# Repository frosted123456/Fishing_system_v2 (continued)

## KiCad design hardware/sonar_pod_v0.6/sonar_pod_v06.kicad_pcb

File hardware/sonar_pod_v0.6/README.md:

# Sonar pod board v0.6: all JLC parts on top, ESP32 module on the bottom

Status: generated, not ordered, not reviewed by a human. DRC: 0 unconnected, 0 clearance (silkscreen and library warnings only).
Netlist check: every pad matches design.py (0 mismatches).
Board: 58 x 53 mm (same as v0.5), 4 layers (F signal / In1 GND / In2 GND / B signal), 1.6 mm, HASL lead-free.

## What changed vs v0.5

| Area | v0.5 | v0.6 | Why |
|---|---|---|---|
| LoRa Ra-01SH (+ C36, C37, R29) | bottom, hand-soldered | **top, JLC-assembled** (lora variant) | one machine-assembled side for everything JLC can place |
| ESP32-S3 module | top, hand-soldered | **bottom, hand-soldered**, under the LoRa module | the only SMD part you solder yourself |
| External ADC (ADS7042 + 5 parts) | DNP option | **removed** | not worth it: the 80 µs ping limits resolution more than the 83 kHz internal ADC; it also lengthened VOUT_I |
| VOUT_I (TUSS → filter) | 26.8 mm, 2 vias | **9.9 mm, 0 vias** | ADC branch and TP3 stub gone |
| TP3 (VOUT test pad) | yes | removed | probe the envelope on R11 |
| Connector pin names | none | **on the silkscreen**: J1 BAT+/BAT−, J2 XA/XB/SH/NTC/NG, J3 3V3/GND/HALL, J4 3V3/GND/BTN/LED, P1 DA/DB/VTX/GND/XA/XB | what to solder where |
| Bottom paste layer | in the gerbers | **removed** | nothing on the bottom is machine-soldered, so no bottom stencil is needed |
| TUSS SPI / IO pin map | see v0.5 | **changed** (see below) | the bottom-mounted module is mirrored, so the bus order flips |

## Orders

| Variant | Assembled parts | BOM lines | Extended types (fee each) |
|---|---|---|---|
| tipup | 59 | 32 | 6: TUSS4470, TPS63020, MT3608, L1, L2, USB-C |
| lora | 63 | 33 | 7: the same + Ra-01SH |

## Noise audit (`src/noise_audit.py`)

| Check | v0.5 | v0.6 |
|---|---|---|
| INP / INN / RINP / FLT | 3.2 / 4.1 / 6.3 / 3.9 mm, 0 vias | 3.2 / 4.1 / 6.0 / 3.9 mm, 0 vias |
| VOUT_I | 26.8 mm, 2 vias, 11 % without reference | **9.9 mm, 0 vias, 0 %** |
| VOUT (to the ESP32 ADC) | 9.5 mm, 0 vias | 10.2 mm, 1 via (the ESP32 pad is on the bottom) |
| GND vias / ground >8 mm from a stitch | 141 / 2 % | 154 / 0 % |
| MT3608 loop / switch node | 4.9 mm² / 6.9 mm | 4.9 mm² / 5.7 mm |
| SGND | 40 mm, 2 vias | 32 mm, 3 vias |
| USB D+ / D− length | 12 / 15 mm | **32 / 36 mm** |

Parallel runs worth knowing about:

| Victim | Aggressor | Run / gap | Assessment |
|---|---|---|---|
| RINP | OUTA | 4.3 mm at 0.54 mm | Harmless. In direct drive OUTA *is* the transducer line that feeds RINP, and OUTA is idle during receive. Transformer mode: gate pulses happen only during transmit. |
| NTC_ADC | SCLK / USB / SDI / SDO | ≤3.8 mm each | slow DC signal with a 100 nF filter |

USB is longer because the module's USB pins now sit at its bottom-right corner. That's fine for full-speed USB at 12 Mbit/s, which tolerates far longer traces.

## ESP32-S3 pin map (v0.6): firmware must be updated

| Function | GPIO | v0.5 |
|---|---|---|
| TUSS NCS | **6** | 8 |
| TUSS SCLK | **7** | 18 |
| TUSS SDI (MOSI) | **15** | 17 |
| TUSS SDO (MISO) | 16 | 16 |
| TUSS IO1 / IO2 | **17 / 18** | 15 / 7 |
| Sonar VOUT (ADC1_CH7) | **8** | 6 |
| VPWR / NTC / VBAT | 4 / 5 / 1 | same |
| HALL / BTN / LED | 2 / 9 / 43 | same |
| Boost EN | 12 | same |
| LoRa NSS / MOSI / MISO / SCK / RXEN / BUSY | 38 / 39 / 40 / 41 / 42 / 44 | same |
| LoRa DIO1 / TXEN / RST | 13 / 14 / 21 | same |
| USB D− / D+ | 19 / 20 | same |
| Free | IO3 (was the ADC CS), IO10 / IO11 on TP7 / TP8 | |

Module: ESP32-S3-WROOM-1U **N4 / N8 / N16 / N8R2**, not the octal-PSRAM variants.

## Ordering

1. PCB: `sonar_pod_v06_gerbers.zip`, 4 layers, 1.6 mm, HASL lead-free, **via covering: tented**. Vias sit under both modules, so they must be covered by solder mask.
2. Assembly: Economic, **top side only**. Upload the BOM + CPL of the variant (`tipup` or `lora`).
3. In the JLC preview, check:
   - **U5 Ra-01SH orientation**: pin 1 (antenna pad) bottom-right, U.FL/IPEX side as on the module drawing
   - pin 1 of U1, U2 and U3
   - the cathode bars of D1, D4, D5 and D6
4. Hand-solder:
   1. **U4 ESP32-S3** on the bottom: edge pads with an iron. For the centre GND pad, use hot air from the bottom or skip it: pins 1/40 are also GND. Hot air on that pad also heats the LoRa module just above it on the top side.
   2. Flash over USB-C.
   3. Fit J1–J4.
5. **Cheaper way to get both variants:** order **10 tipup boards** in one order, then hand-solder a Ra-01SH (castellated 2 mm pads, easy with an iron) + C36/C37/R29 on the boards that need LoRa. A second order costs the fixed fees again (about C$52 for PCB + setup + stencil + extended fees).

## Option fitting (unchanged from v0.5, minus the ADC)

| Mode | Fit | Remove / change |
|---|---|---|
| Direct drive (as ordered) | — | — (L3, C43 optional) |
| Transformer drive | Q1, Q2 (AP1002), R42/R43 10R, R44/R45 10k, R46 0R, C44 10 µF 50 V (designator hidden: the 1206 pad pair right of P1), transformer on P1, D7 BAV99 | remove R40, R41; R8B 0R → 1k–2.2k 1206; bridge P1 pins 4–6 |

## Risks and open items

| # | Item | Severity |
|---|---|---|
| 1 | Firmware pin map changed (TUSS bus and VOUT). The firmware port to the S3 does not exist yet. | must do |
| 2 | Transformer mode: TUSS4470 pre-driver mode with VDRV from the internal regulator is undocumented. R8B pulse power ~6 W for ~80 µs. Transformer not sourced. | high (option only) |
| 3 | Vias under both modules: they must be tented. | medium |
| 4 | U5 orientation in the JLC preview not yet confirmed. Only the SOT-23-6 rotation correction is applied. | medium |
| 5 | U2 TPS63020 footprint self-drawn; AP1002 pinout from LCSC. | medium |
| 6 | No ESD on USB; autorouted, not hand-polished. | low |

## Files

- `sonar_pod_v06.kicad_pro/.kicad_sch/.kicad_pcb`, `sonar_pod_v06_schematic.pdf`, `sonar_pod_v06.step`
- `routed_f.png`, `routed_b.png` (bottom, mirrored view), `audit/noise_v06.png`, `audit/noise_v06.json`
- `sonar_pod_v06_gerbers.zip`, JLC CSVs, `.xlsx` BOM and centroid per variant
- `src/`: full pipeline (`build.sh`, `post.sh`, `v06.ses`)

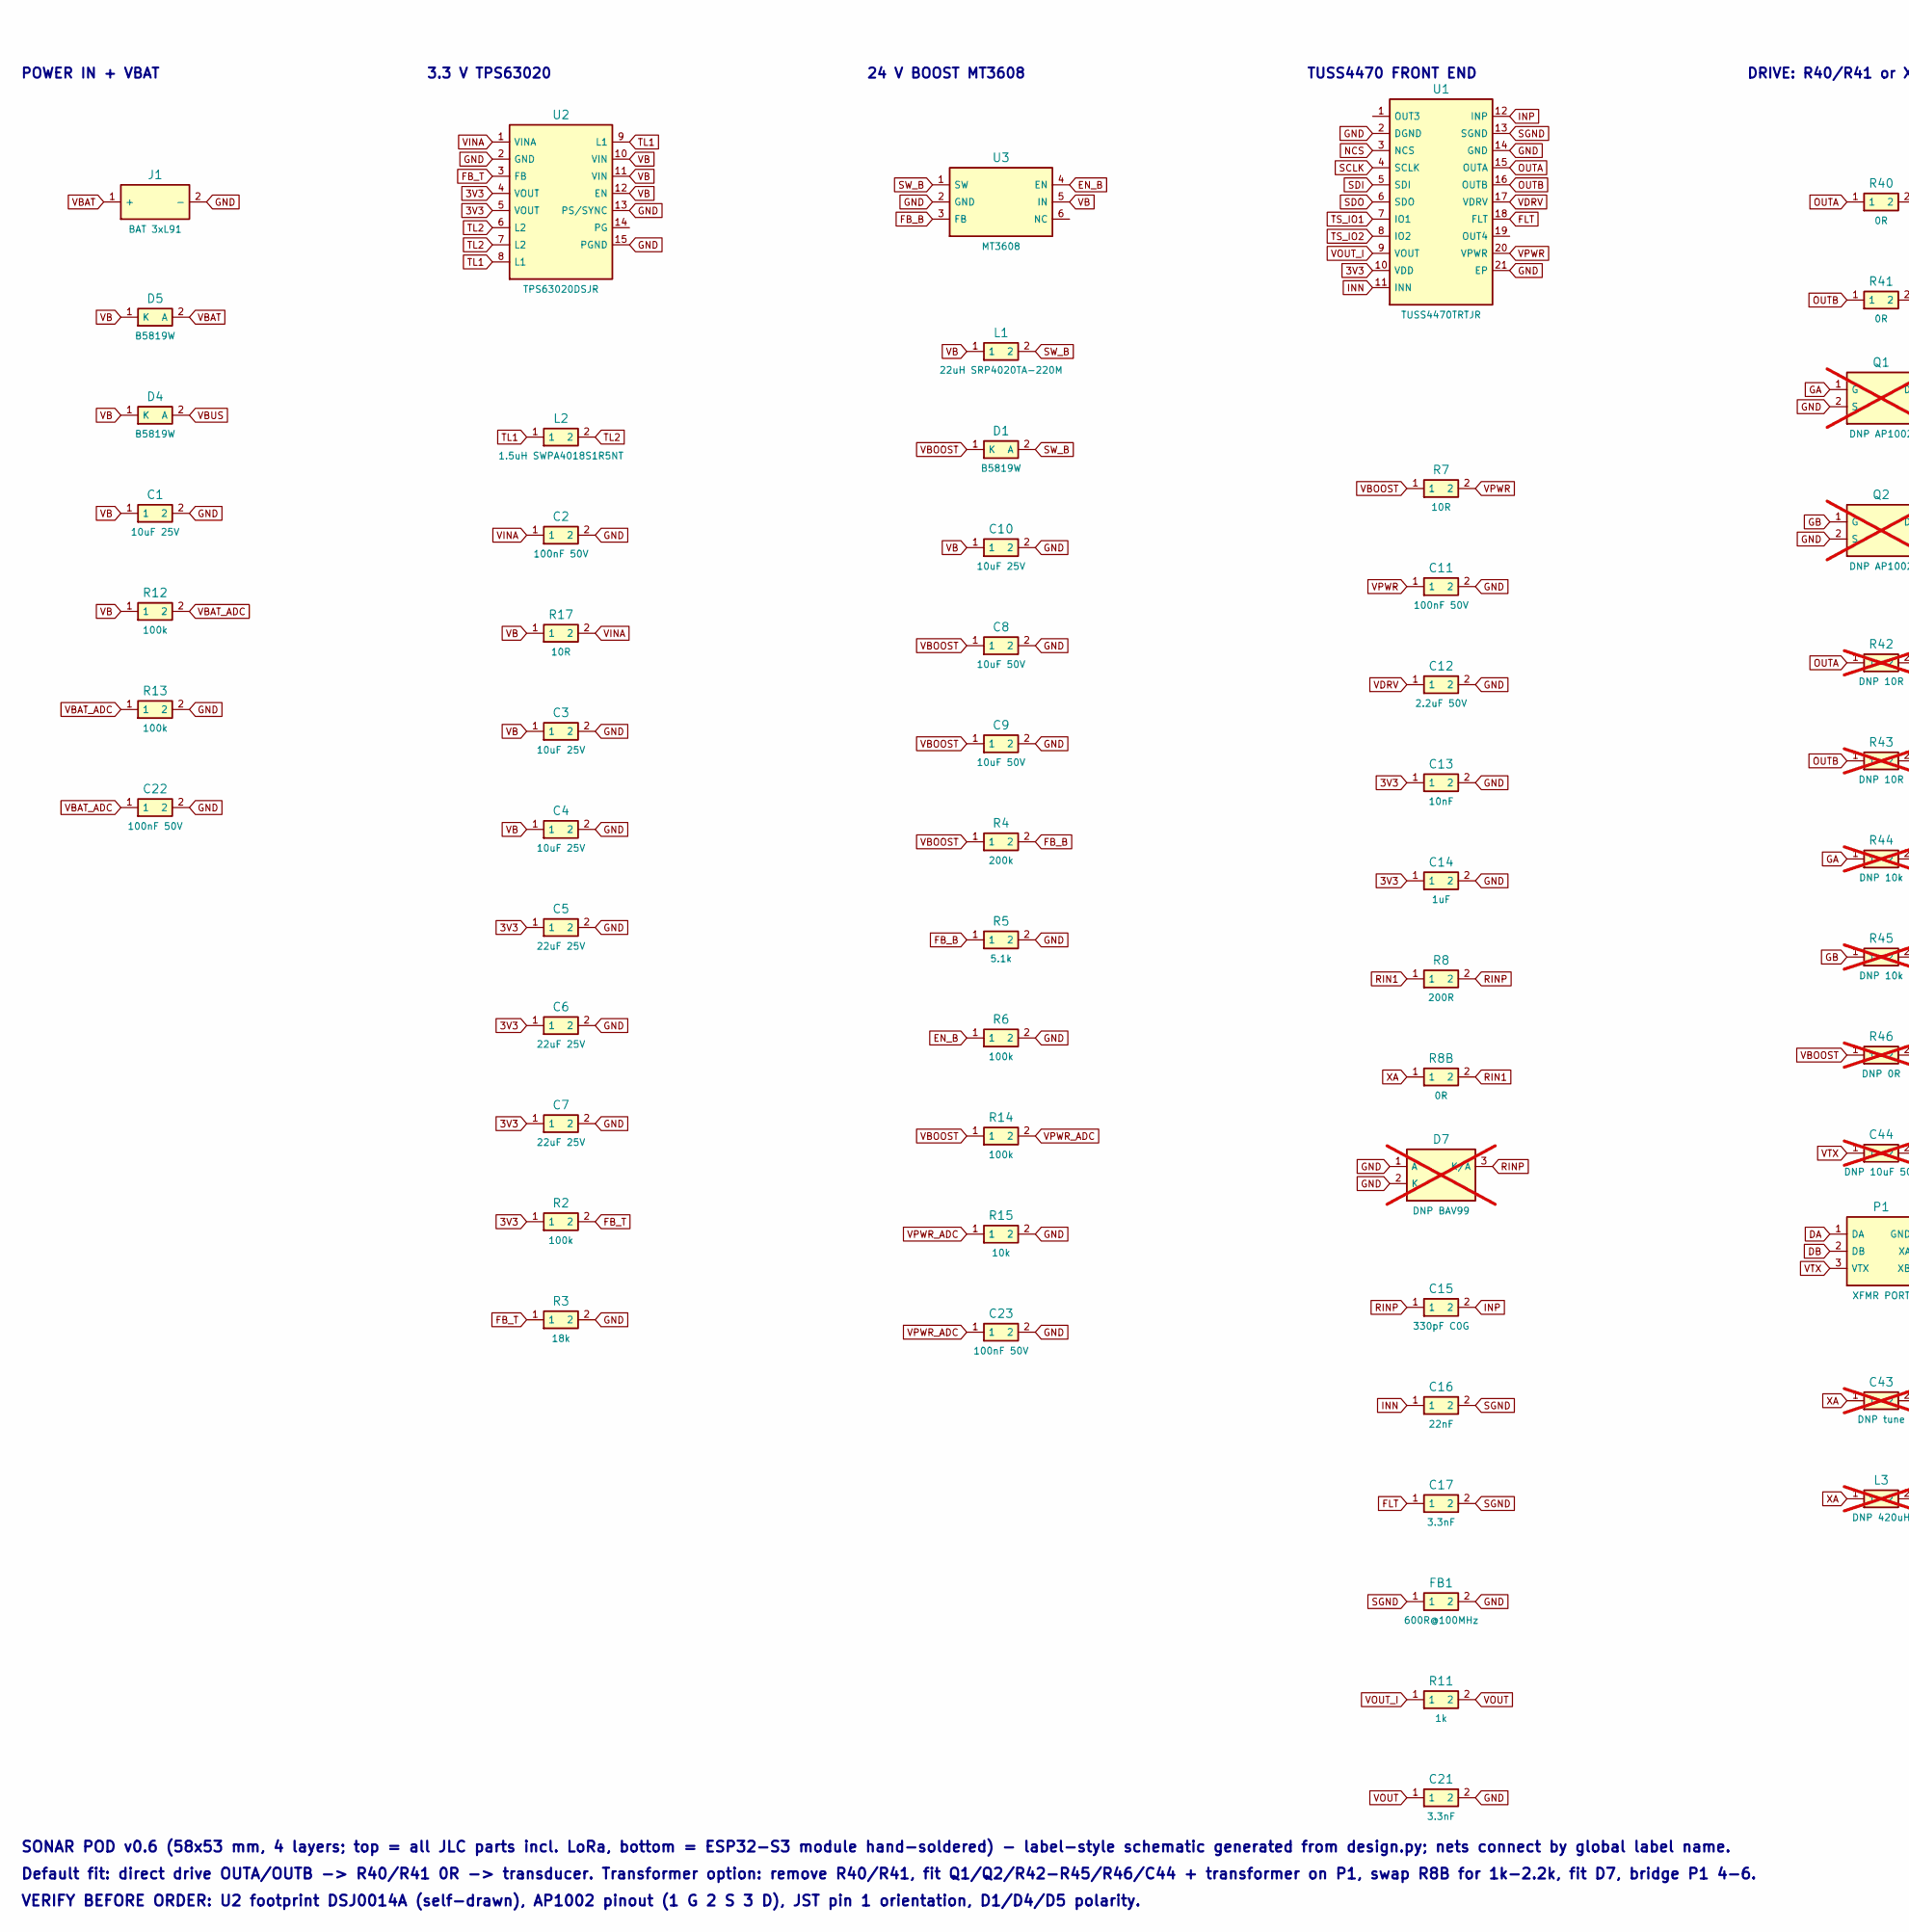
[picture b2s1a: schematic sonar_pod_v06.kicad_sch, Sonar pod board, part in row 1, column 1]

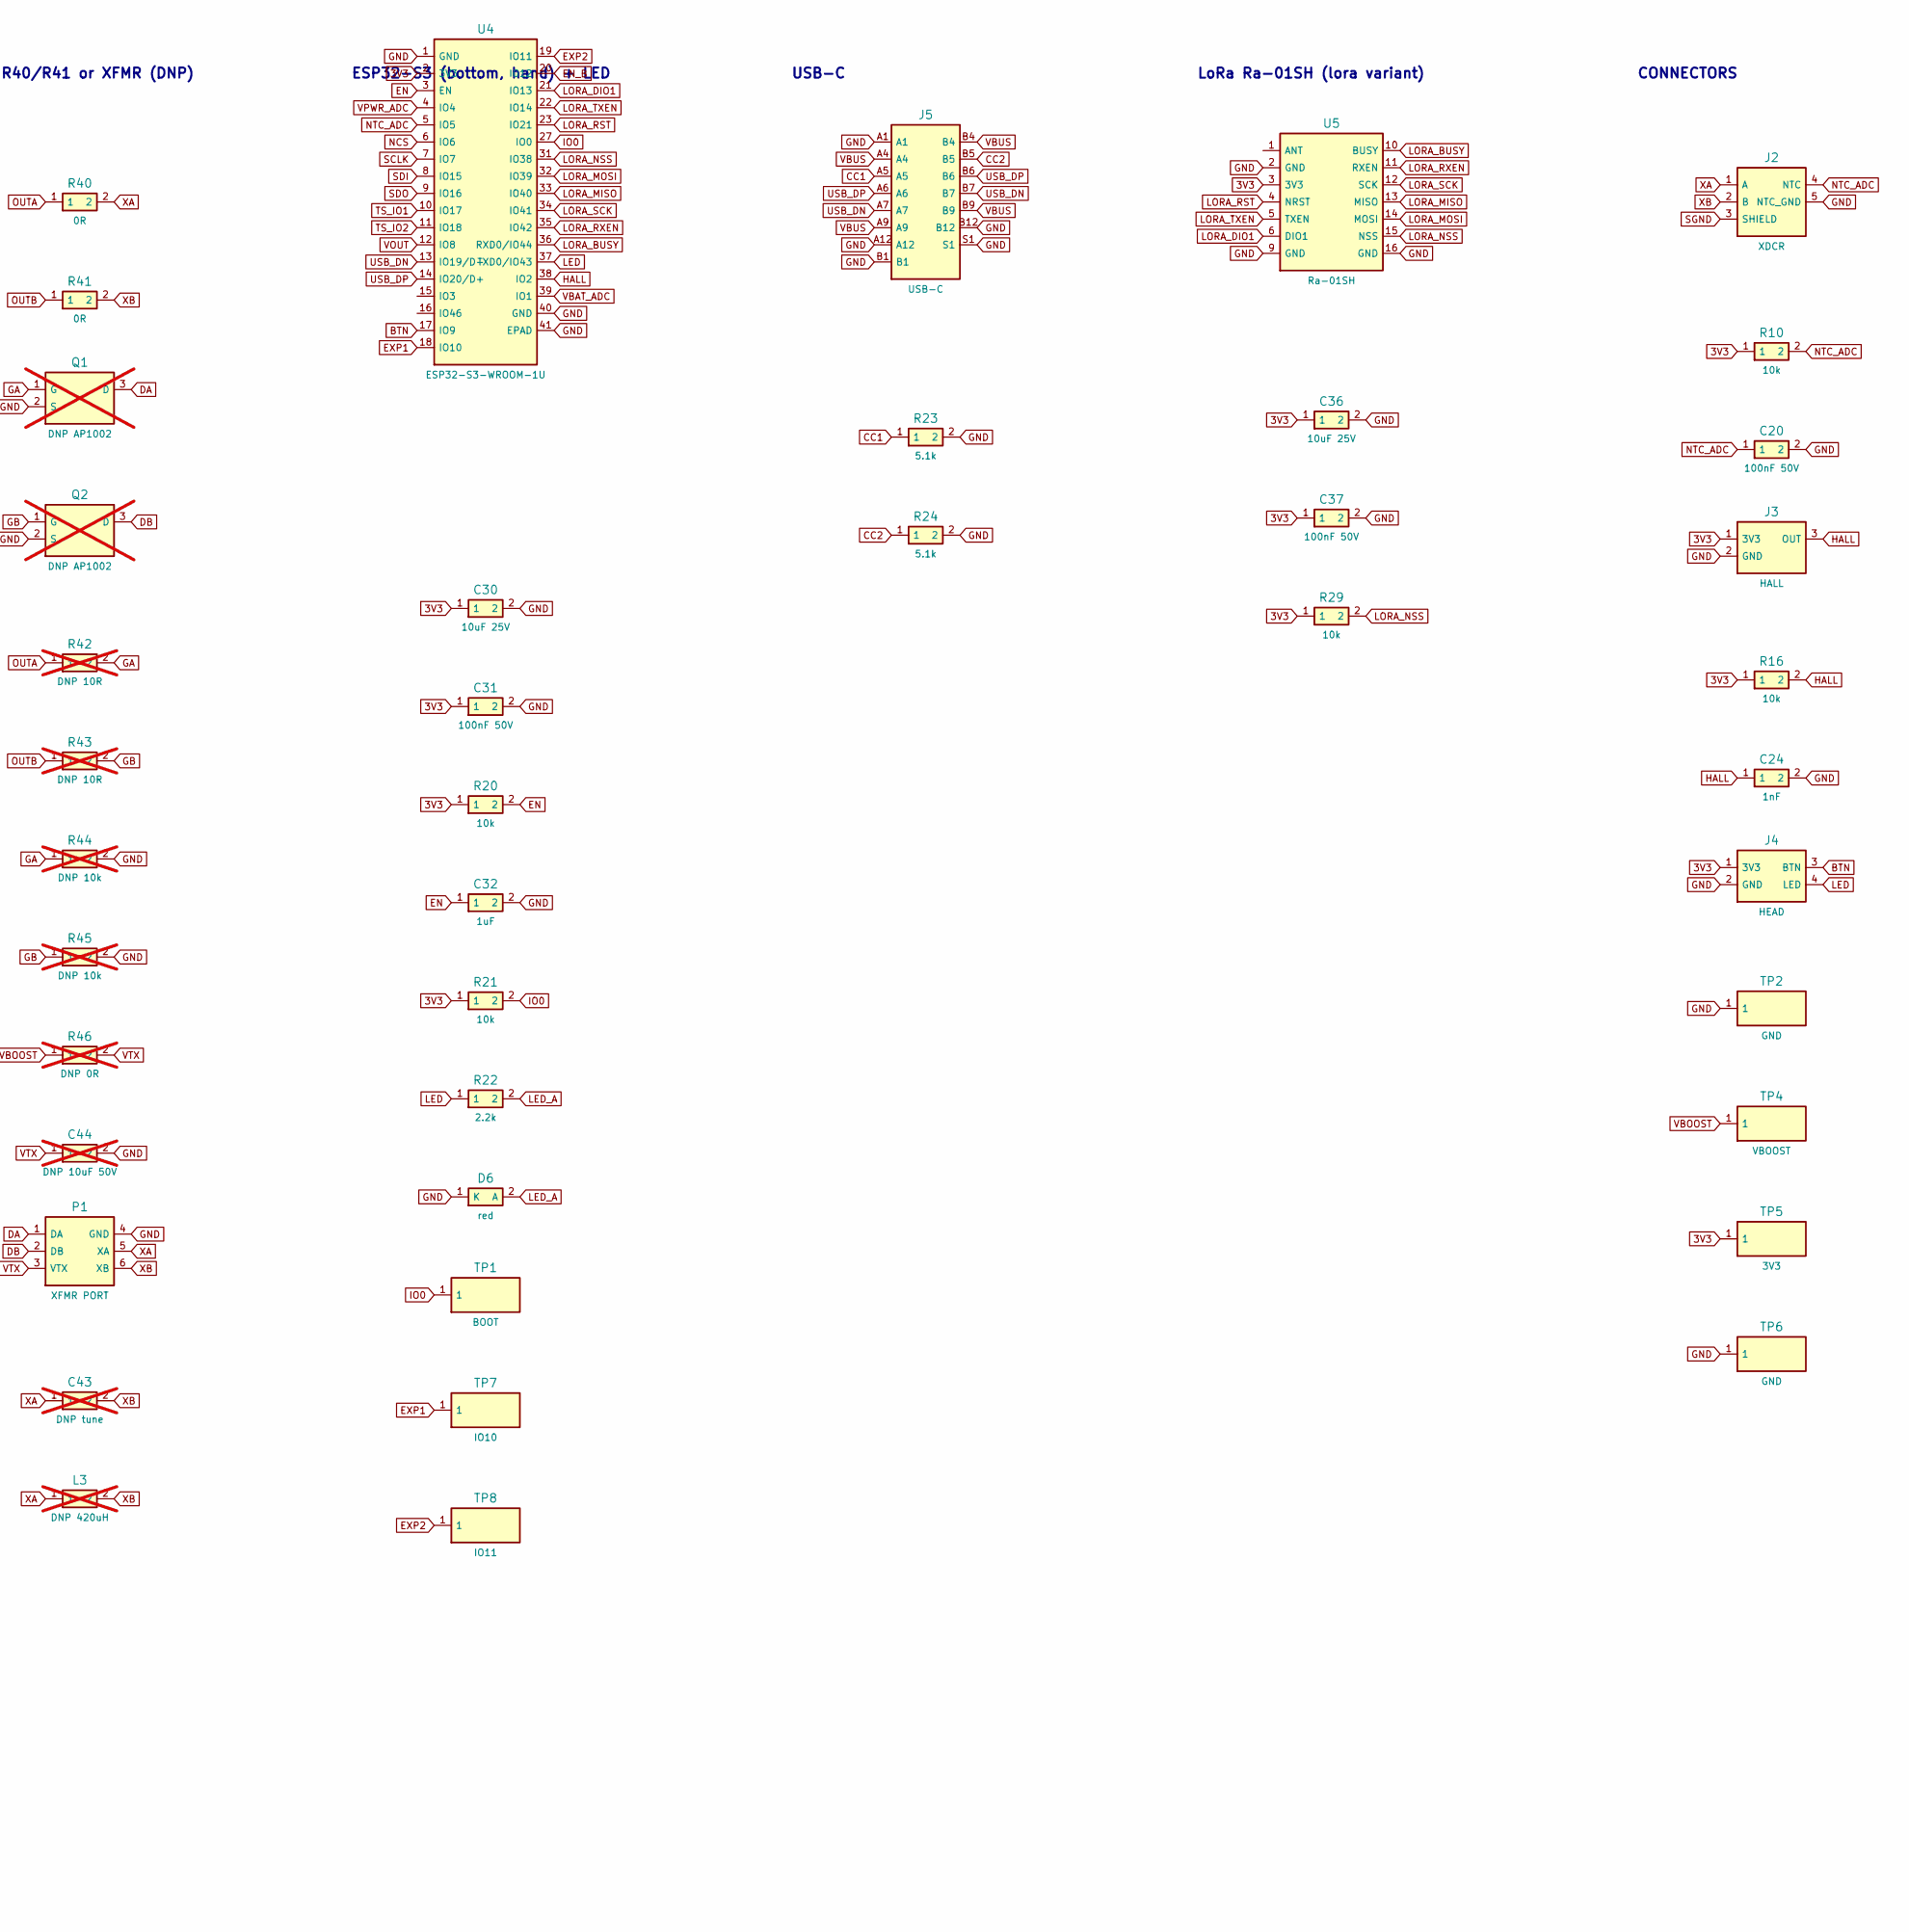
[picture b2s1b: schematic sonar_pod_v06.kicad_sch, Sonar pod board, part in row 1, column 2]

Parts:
C1, C3, C4, C10, C30, C36: 10uF 25V; C_0805_2012Metric; LCSC C15850
C2, C11, C20, C22, C23, C31, C37: 100nF 50V; C_0603_1608Metric; LCSC C14663
C5, C6, C7: 22uF 25V; C_0805_2012Metric; LCSC C45783
C8, C9: 10uF 50V; C_1206_3216Metric; LCSC C13585
C12: 2.2uF 50V; C_1206_3216Metric; LCSC C50254
C13: 10nF; C_0603_1608Metric; LCSC C57112
C14, C32: 1uF; C_0603_1608Metric; LCSC C15849
C15: 330pF C0G; C_0603_1608Metric; LCSC C1664
C16: 22nF; C_0603_1608Metric; LCSC C21122
C17, C21: 3.3nF; C_0603_1608Metric; LCSC C1613
C24: 1nF; C_0603_1608Metric; LCSC C1588
C43: DNP tune; C_1206_3216Metric; not fitted
C44: DNP 10uF 50V; C_1206_3216Metric; not fitted
D1, D4, D5: B5819W; D_SOD-123; LCSC C8598
D6: red; LED_0603_1608Metric; LCSC C2286
D7: DNP BAV99; SOT-23; LCSC C2500; not fitted
FB1: 600R@100MHz; L_0805_2012Metric; LCSC C1017
J1: BAT 3xL91; JST_XH_B2B-XH-A_1x02_P2.50mm_Vertical
J2: XDCR; JST_XH_B5B-XH-A_1x05_P2.50mm_Vertical
J3: HALL; JST_XH_B3B-XH-A_1x03_P2.50mm_Vertical
J4: HEAD; JST_PH_B4B-PH-K_1x04_P2.00mm_Vertical
J5: USB-C; USB_C_Receptacle_HRO_TYPE-C-31-M-12; LCSC C165948
L1: 22uH SRP4020TA-220M; L_Sunlord_SWPA4020S; LCSC C1847949
L2: 1.5uH SWPA4018S1R5NT; L_Sunlord_SWPA4020S; LCSC C80662
L3: DNP 420uH; L_Sunlord_SWPA4020S; not fitted
P1: XFMR PORT; PinHeader_2x03_P2.54mm_Vertical
Q1, Q2: DNP AP1002; SOT-23; LCSC C2995324; not fitted
R2, R6, R12, R13, R14: 100k; R_0603_1608Metric; LCSC C25803
R3: 18k; R_0603_1608Metric; LCSC C25810
R4: 200k; R_0603_1608Metric; LCSC C25811
R5, R23, R24: 5.1k; R_0603_1608Metric; LCSC C23186
R7: 10R; R_0805_2012Metric; LCSC C17415
R8: 200R; R_0603_1608Metric; LCSC C8218
R8B: 0R; R_1206_3216Metric; LCSC C17888
R10, R15, R16, R20, R21, R29: 10k; R_0603_1608Metric; LCSC C25804
R11: 1k; R_0603_1608Metric; LCSC C21190
R17: 10R; R_0603_1608Metric; LCSC C22859
R22: 2.2k; R_0603_1608Metric; LCSC C4190
R40, R41: 0R; R_0603_1608Metric; LCSC C21189
R42, R43: DNP 10R; R_0603_1608Metric; not fitted
R44, R45: DNP 10k; R_0603_1608Metric; not fitted
R46: DNP 0R; R_0805_2012Metric; not fitted
TP1: BOOT; TestPoint_Pad_1.0x1.0mm
TP2, TP6: GND; TestPoint_Pad_1.0x1.0mm
TP4: VBOOST; TestPoint_Pad_1.0x1.0mm
TP5: 3V3; TestPoint_Pad_1.0x1.0mm
TP7: IO10; TestPoint_Pad_1.0x1.0mm
TP8: IO11; TestPoint_Pad_1.0x1.0mm
U1: TUSS4470TRTJR; QFN-20-1EP_4x4mm_P0.5mm_EP2.5x2.5mm; LCSC C1855776
U2: TPS63020DSJR; Texas_DSJ0014A; LCSC C15483
U3: MT3608; SOT-23-6; LCSC C84817
U4: ESP32-S3-WROOM-1U; LCSC C2980297
U5: Ra-01SH; Ai-Thinker-Ra-01-LoRa; LCSC C2764087

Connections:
3V3: C5.1, C6.1, C7.1, C13.1, C14.1, C30.1, C31.1, C36.1, C37.1, J3.1 (3V3), J4.1 (3V3), R2.1, R10.1, R16.1, R20.1, R21.1, R29.1, TP5.1, U1.10 (VDD), U2.4 (VOUT), U2.5 (VOUT), U4.2 (3V3), U5.3 (3V3)
BTN: J4.3 (BTN), U4.17 (IO9)
CC1: J5.A5, R23.1
CC2: J5.B5, R24.1
DA: P1.1 (DA), Q1.3 (D)
DB: P1.2 (DB), Q2.3 (D)
EN: C32.1, R20.2, U4.3 (EN)
EN_B: R6.1, U3.4 (EN), U4.20 (IO12)
EXP1: TP7.1, U4.18 (IO10)
EXP2: TP8.1, U4.19 (IO11)
FB_B: R4.2, R5.1, U3.3 (FB)
FB_T: R2.2, R3.1, U2.3 (FB)
FLT: C17.1, U1.18 (FLT)
GA: Q1.1 (G), R42.2, R44.1
GB: Q2.1 (G), R43.2, R45.1
GND: C1.2, C2.2, C3.2, C4.2, C5.2, C6.2, C7.2, C8.2, C9.2, C10.2, C11.2, C12.2, C13.2, C14.2, C20.2, C21.2, C22.2, C23.2, C24.2, C30.2, C31.2, C32.2, C36.2, C37.2, C44.2, D6.1 (K), D7.1 (A), D7.2 (K), FB1.2, J1.2 (-), J2.5 (NTC_GND), J3.2 (GND), J4.2 (GND), J5.A1, J5.A12, J5.B1, J5.B12, J5.S1, P1.4 (GND), Q1.2 (S), Q2.2 (S), R3.2, R5.2, R6.2, R13.2, R15.2, R23.2, R24.2, R44.2, R45.2, TP2.1, TP6.1, U1.2 (DGND), U1.14 (GND), U1.21 (EP), U2.2 (GND), U2.13 (PS/SYNC), U2.15 (PGND), U3.2 (GND), U4.1 (GND), U4.40 (GND), U4.41 (EPAD), U5.2 (GND), U5.9 (GND), U5.16 (GND)
HALL: C24.1, J3.3 (OUT), R16.2, U4.38 (IO2)
INN: C16.1, U1.11 (INN)
INP: C15.2, U1.12 (INP)
IO0: R21.2, TP1.1, U4.27 (IO0)
LED: J4.4 (LED), R22.1, U4.37 (TXD0/IO43)
LED_A: D6.2 (A), R22.2
LORA_BUSY: U4.36 (RXD0/IO44), U5.10 (BUSY)
LORA_DIO1: U4.21 (IO13), U5.6 (DIO1)
LORA_MISO: U4.33 (IO40), U5.13 (MISO)
LORA_MOSI: U4.32 (IO39), U5.14 (MOSI)
LORA_NSS: R29.2, U4.31 (IO38), U5.15 (NSS)
LORA_RST: U4.23 (IO21), U5.4 (NRST)
LORA_RXEN: U4.35 (IO42), U5.11 (RXEN)
LORA_SCK: U4.34 (IO41), U5.12 (SCK)
LORA_TXEN: U4.22 (IO14), U5.5 (TXEN)
NCS: U1.3 (NCS), U4.6 (IO6)
NTC_ADC: C20.1, J2.4 (NTC), R10.2, U4.5 (IO5)
OUTA: R40.1, R42.1, U1.15 (OUTA)
OUTB: R41.1, R43.1, U1.16 (OUTB)
RIN1: R8.1, R8B.2
RINP: C15.1, D7.3 (K/A), R8.2
SCLK: U1.4 (SCLK), U4.7 (IO7)
SDI: U1.5 (SDI), U4.8 (IO15)
SDO: U1.6 (SDO), U4.9 (IO16)
SGND: C16.2, C17.2, FB1.1, J2.3 (SHIELD), U1.13 (SGND)
SW_B: D1.2 (A), L1.2, U3.1 (SW)
TL1: L2.1, U2.8 (L1), U2.9 (L1)
TL2: L2.2, U2.6 (L2), U2.7 (L2)
TS_IO1: U1.7 (IO1), U4.10 (IO17)
TS_IO2: U1.8 (IO2), U4.11 (IO18)
USB_DN: J5.A7, J5.B7, U4.13 (IO19/D-)
USB_DP: J5.A6, J5.B6, U4.14 (IO20/D+)
VB: C1.1, C3.1, C4.1, C10.1, D4.1 (K), D5.1 (K), L1.1, R12.1, R17.1, U2.10 (VIN), U2.11 (VIN), U2.12 (EN), U3.5 (IN)
VBAT: D5.2 (A), J1.1 (+)
VBAT_ADC: C22.1, R12.2, R13.1, U4.39 (IO1)
VBOOST: C8.1, C9.1, D1.1 (K), R4.1, R7.1, R14.1, R46.1, TP4.1
VBUS: D4.2 (A), J5.A4, J5.A9, J5.B4, J5.B9
VDRV: C12.1, U1.17 (VDRV)
VINA: C2.1, R17.2, U2.1 (VINA)
VOUT: C21.1, R11.2, U4.12 (IO8)
VOUT_I: R11.1, U1.9 (VOUT)
VPWR: C11.1, R7.2, U1.20 (VPWR)
VPWR_ADC: C23.1, R14.2, R15.1, U4.4 (IO4)
VTX: C44.1, P1.3 (VTX), R46.2
XA: C43.1, J2.1 (A), L3.1, P1.5 (XA), R8B.1, R40.2
XB: C43.2, J2.2 (B), L3.2, P1.6 (XB), R41.2

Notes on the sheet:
POWER IN + VBAT
3.3 V TPS63020
24 V BOOST MT3608
TUSS4470 FRONT END
DRIVE: R40/R41 or XFMR (DNP)
ESP32-S3 (bottom, hand) + LED
USB-C
LoRa Ra-01SH (lora variant)
CONNECTORS
SONAR POD v0.6 (58x53 mm, 4 layers; top = all JLC parts incl. LoRa, bottom = ESP32-S3 module hand-soldered) - label-style schematic generated from design.py; nets connect by global label name.
Default fit: direct drive OUTA/OUTB -> R40/R41 0R -> transducer. Transformer option: remove R40/R41, fit Q1/Q2/R42-R45/R46/C44 + transformer on P1, swap R8B for 1k-2.2k, fit D7, bridge P1 4-6.
VERIFY BEFORE ORDER: U2 footprint DSJ0014A (self-drawn), AP1002 pinout (1 G 2 S 3 D), JST pin 1 orientation, D1/D4/D5 polarity.

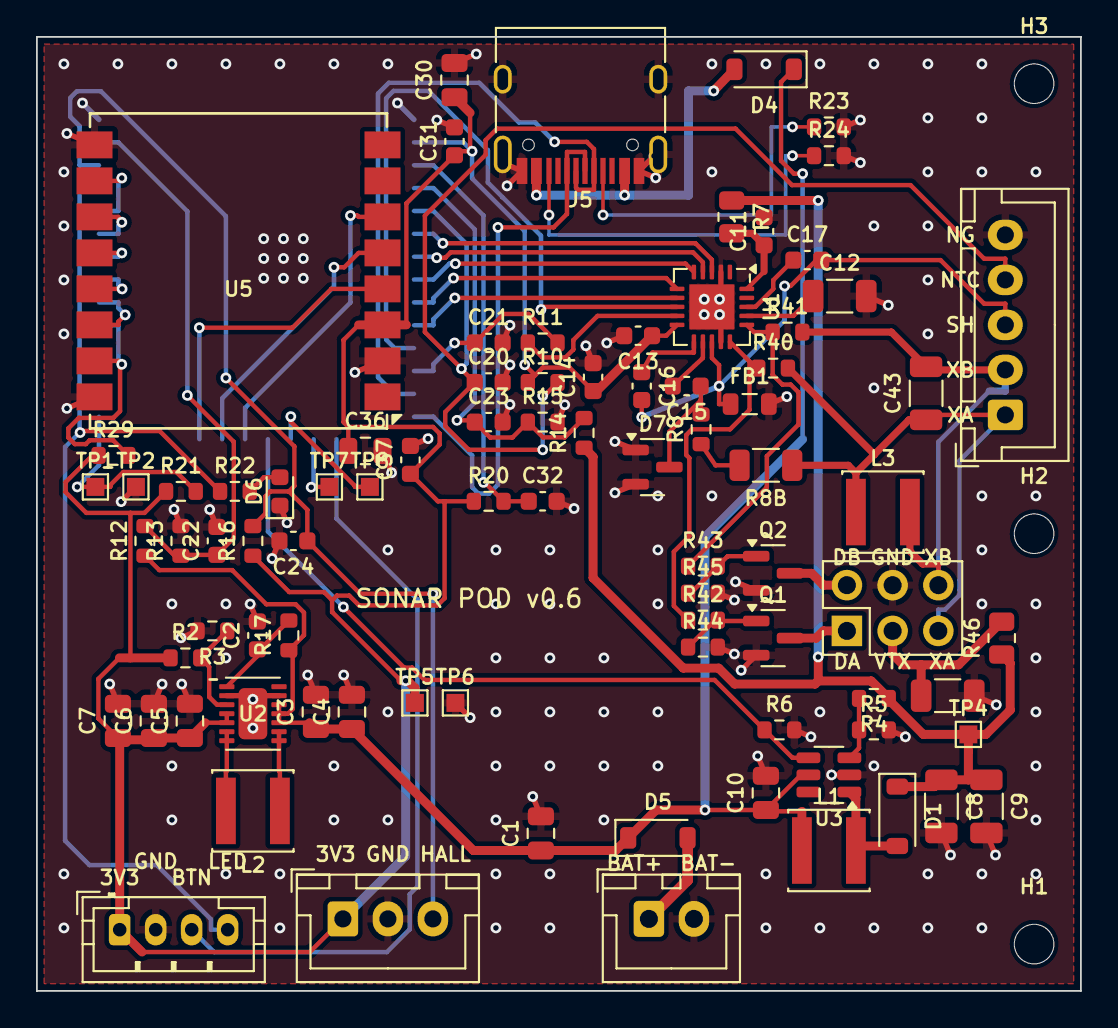
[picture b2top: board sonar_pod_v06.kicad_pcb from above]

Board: 4 copper layers, 58.0 x 53.0 mm, 90 parts (1 on the bottom side), 62 nets.

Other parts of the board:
H1, H2, H3: M2; MountingHole_2.2mm_M2

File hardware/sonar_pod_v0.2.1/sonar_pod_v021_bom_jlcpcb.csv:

Comment,Designator,Footprint,LCSC Part #
AO3401A,Q1,SOT-23,C15127
100k,"R1,R2,R6,R12,R13,R14",R_0603_1608Metric,C25803
10uF 25V,"C1,C3,C4,C10",C_0805_2012Metric,C15850
TPS63020DSJR,U2,Texas_DSJ0014A,C15483
1.5uH SWPA4018S1R5NT,L2,L_Sunlord_SWPA4020S,C80662
18k,R3,R_0603_1608Metric,C25810
100nF 50V,"C2,C11,C22,C23,C20",C_0603_1608Metric,C14663
10R,R17,R_0603_1608Metric,C22859
22uF 25V,"C5,C6,C7",C_0805_2012Metric,C45783
MT3608,U3,SOT-23-6,C84817
22uH SRP4020TA-220M,L1,L_Sunlord_SWPA4020S,C1847949
B5819W,D1,D_SOD-123,C8598
10uF 50V,"C8,C9",C_1206_3216Metric,C13585
200k,R4,R_0603_1608Metric,C25811
5.1k,R5,R_0603_1608Metric,C23186
TUSS4470TRTJR,U1,QFN-20-1EP_4x4mm_P0.5mm_EP2.5x2.5mm,C1855776
10R,R7,R_0805_2012Metric,C17415
2.2uF 50V,C12,C_1206_3216Metric,C50254
10nF,C13,C_0603_1608Metric,C57112
1uF,C14,C_0603_1608Metric,C15849
200R,R8,R_0603_1608Metric,C8218
330pF C0G,C15,C_0603_1608Metric,C1664
22nF,C16,C_0603_1608Metric,C21122
3.3nF,C17,C_0603_1608Metric,C1613
600R@100MHz,FB1,L_0805_2012Metric,C1017
100R,R11,R_0603_1608Metric,C22775
1nF,"C21,C24",C_0603_1608Metric,C1588
10k,"R15,R10,R16",R_0603_1608Metric,C25804

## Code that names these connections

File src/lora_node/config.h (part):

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#define OLED_ADDRESS        0x3C        // I2C address

// LoRa Radio (SX1262)
#define LORA_SCK            9
#define LORA_MISO           11
#define LORA_MOSI           10
#define LORA_CS             8
#define LORA_RST            12
#define LORA_DIO1           14
#define LORA_BUSY           13

// User IO
#define LED_PIN             35          // Onboard white LED
#define USER_BUTTON         0           // PRG/BOOT button (screen, silence, hotspot)
#ifndef BTN_PIN
#define BTN_PIN             5           // D61 arming button to GND (internal pull-up), hub / LoRa tip-up hole; -1 = none
#endif

// External connections
#define BUZZER_PIN          7           // CLT1036 active buzzer
#define REED_PIN            4           // Own hole sensor (hub / LoRa tip-up): reed switch or Hall latch output
// D64: the own hole can be a spool-shaft Hall latch (US1881 + alternating magnets, like the WROOM head: a trip is
// TRIGGER_FLIPS flips within HALL_WINDOW_MS, over after HALL_CLEAR_SEC still) or a plain reed (level + the OLED
// "Reed polarity" setting). Same knobs as src/sensor_node/config.h. Build flag -D HOLE_HALL_LATCH=0 for a reed.
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
// ═══════════════════════════════════════════════════════════════════════════
// SONAR (D62): TUSS4470 shield 002 on the module's own hole (hub, LoRa tip-up, relay with a hole; not the chalet)
// Pins: lib/SonarTuss/src/sonar_tuss4470.h (Heltec V3 block: SCK 47, MOSI 48, MISO 33, CS 34, IO1 38, IO2 39, VOUT 6).
// ═══════════════════════════════════════════════════════════════════════════

#ifndef SONAR_REAL
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
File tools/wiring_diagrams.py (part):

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        left=[("3V3 pin (fed)", ORANGE), ("GND", BLACK), ("GPIO4 hole", GREEN), ("GPIO2 VBAT", RED), ("GPIO5 button", GREEN)],
        notes=["GPIO0 PRG (screen)", "JST: nothing (no LiPo)", "LED 35, buzzer 7", "LoRa 8-14, OLED 17/18/21", "USB-C: flash / charge"],
        en="GPIO40 conv. enable",
        right=["GPIO47 SCLK", "GPIO33 MISO", "GPIO48 MOSI", "GPIO34 NCS", "GPIO38 IO1", "GPIO39 IO2 burst", "GPIO6 echo"],
        hall=("Own hole sensor", "reed or Hall latch (REED_PIN 4)", "VDD ← VBAT (Hall only; 3.5 V min)", "OUT → GPIO4",
              "reed: GPIO4 to GND. US1881: 1 VDD, 2 GND, 3 OUT"),
        sense=("two 100 k, tap on GPIO2", "GPIO2"),
        button=("GPIO5", "short = arm / disarm, press while FISH ON = clear, hold 3 s = report"),
        foot=[(RED, "Never 5 V on the shield's \"5V\" pin (TUSS4470 logic supply): feed it from the 3.3 V rail."),
              (RED, "Pack switch OFF while USB is plugged: the Heltec's own regulator drives the same 3V3 rail. Nothing on the JST (no LiPo, no charger in use)."),
              (GREY, "A0 / VOUT must stay below ~3.1 V at GPIO6. Twist the A0 wire with its own GND wire. Battery read = the 2:1 divider on GPIO2, not the onboard VBAT_Read."),
              (GREY, "XL6009: set 31.5 V with a meter before wiring anything. Wire A into the J4 middle pin only. Wire B never without the DB107 + 1N4148 (VDRV must stay below VPWR)."),
              (GREY, "Enable wire: the module ties chip pin 2 (EN) to VIN. Cut that pin free of its pad, lift it, solder a thin wire (30 AWG) from the pin to GPIO40. No resistor."),
              (GREY, "Flash: python tools/flash.py hub --id N --sonar --gate (or sensor_lora). Check: web page, Settings, Advanced, Wiring check: \"Converter enable wire OK\"."),
              (GREY, "20 V build instead: MT3608 at 21.5 V into the J4 middle pin, no wire B, no enable wire, flash without --gate. Same pins otherwise.")]),
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        title="WROOM sonar tip-up: wiring",
        sub="ESP32 DevKit V1 (30 pin) + TUSS4470 shield 002, 30 V drive build with the converter enable wire (README 4.4.6)",
        mcu=("ESP32 DevKit V1", "ESP32-WROOM-32, 30 pins"),
        left=[("3V3 pin (input)", ORANGE), ("GND", BLACK), ("GPIO27 Hall", GREEN), ("GPIO34 VBAT sense", RED), ("GPIO33 arming button", GREEN)],
        notes=["GPIO2 LED (on board)", "USB: flashing only"],
        en="D13 conv. enable",
        right=["D18 SCLK", "D19 MISO", "D23 MOSI", "D5 NCS", "D26 IO1", "D25 IO2 burst", "VP = GPIO36 echo"],
        hall=("Hall latch US1881", "spool shaft, 4 alternating magnets", "VDD ← VBAT (3.5-24 V spec)", "OUT → GPIO27",
              "US1881: 1 VDD (pack), 2 GND, 3 OUT open drain"),
        sense=("two 100 k, max 2.7 V at the pin", "GPIO34"),
        button=("GPIO33", "short = arm / disarm, press while tripped = clear, hold 3 s = report"),
        foot=[(RED, "Never 5 V on the shield's \"5V\" pin: it is the TUSS4470 logic supply; 5 V there puts more than 3.6 V on ESP32 pins."),
              (GREY, "A0 / VOUT must stay below ~3.1 V at GPIO36. Twist the A0 wire with its own GND wire."),
              (GREY, "ESP32 fed on its 3V3 pin. Pack switch OFF while USB is plugged: the devkit's own regulator drives the same 3V3 rail."),
              (GREY, "XL6009: set 31.5 V with a meter before wiring anything. Wire A into the J4 middle pin only. Wire B never without the DB107 + 1N4148 (VDRV must stay below VPWR)."),
              (GREY, "Enable wire: the module ties chip pin 2 (EN) to VIN. Cut that pin free of its pad, lift it, solder a thin wire (30 AWG) from the pin to D13 (GPIO13). No resistor."),
              (GREY, "Flash: python tools/flash.py tipup_wroom --id N --sonar --gate. The 30 V build and the enable wire are proven on the Heltec hub; not yet tried on a WROOM."),
              (GREY, "20 V build instead: MT3608 at 21.5 V into the J4 middle pin, no wire B, no enable wire, flash without --gate. Same pins otherwise.")]),
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    s.box(60, 125, 300, 140, RED, "#faf0ee", "3 x L91 lithium AA", "holder switch in series", 20)
    s.pin(360, 200, "+", RED, "r"); s.pin(360, 240, "−", BLACK, "r")
    s.box(560, 125, 320, 140, ORANGE, "#fff3ee", "TPS63020 module", "buck-boost → 3.3 V", 20)
    s.pin(560, 200, "VIN", RED, "l"); s.pin(560, 240, "GND", BLACK, "l"); s.pin(880, 200, "VOUT", ORANGE, "r"); s.pin(880, 240, "GND", BLACK, "r")
    s.box(560, 305, 320, 185, PURPLE, "#f4eef7", "XL6009 module", "boost, trimpot set to 31.5 V", 20)
    s.pin(560, 395, "VIN", RED, "l"); s.pin(560, 435, "GND", BLACK, "l"); s.pin(880, 395, "VOUT", PURPLE, "r"); s.pin(880, 435, "GND", BLACK, "r")
    s.dot(720, 490, PINK); s.text(720, 468, "EN = chip pin 2, cut free", PINK, 12.5, "center")

    # ---- boards ----
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    # ---- hole sensor, battery sense, button ----
    HY = 1300
    s.box(260, HY, 360, 150, GREEN, "#f0f5ef", cfg["hall"][0], cfg["hall"][1], 20)
    s.pin(260, HY + 80, cfg["hall"][2], RED, "l"); s.pin(260, HY + 120, "GND", BLACK, "l"); s.pin(620, HY + 100, cfg["hall"][3], GREEN, "r")
    s.text(262, HY + 169, cfg["hall"][4], GREY, 10)
    s.box(260, HY + 190, 360, 150, RED, "#faf0ee", "Battery sense 2:1", cfg["sense"][0], 20)
    s.text(290, HY + 278, "VBAT ─ 100k ─┬─ 100k ─ GND", BLACK, 15); s.text(290, HY + 311, "             └─ " + cfg["sense"][1], BLACK, 15)
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
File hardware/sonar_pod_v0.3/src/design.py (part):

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part("C1", "10uF 10V", C0805, {1: "VB", 2: "GND"}, (16.5, 5.5), rot=0, lcsc="C15850", desc="input bulk")

# ---------------- 3.3 V buck-boost TPS63020 ----------------
# DSJ0014A pins: 1 VINA 2 GND 3 FB 4,5 VOUT 6,7 L2 8,9 L1 10,11 VIN 12 EN 13 PS/SYNC 14 PG, 15 = PGND pad
part("U2", "TPS63020DSJR", "SonarPod:Texas_DSJ0014A", {1: "VINA", 2: "GND", 3: "FB_T", 4: "3V3", 5: "3V3", 6: "TL2", 7: "TL2", 8: "TL1", 9: "TL1", 10: "VB", 11: "VB", 12: "VB", 13: "GND", 14: "", 15: "GND"},
     (15.5, 13.5), rot=0, lcsc="C15483", desc="buck-boost 3.3 V 3 A; EN=VIN, PS/SYNC=GND (power save)")
part("L2", "1.5uH XFL4020", "Inductor_SMD:L_Coilcraft_XxL4020", {1: "TL1", 2: "TL2"}, (15.5, 19.5), rot=0, lcsc="C150393", desc="Coilcraft XFL4020-152ME or equivalent 4x4 1.5uH >4 A", mfr="XFL4020-152MEB")
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     {1: "", 2: "GND", 3: "NCS", 4: "SCLK", 5: "SDI", 6: "SDO", 7: "IO1", 8: "IO2", 9: "VOUT_I", 10: "3V3", 11: "INN", 12: "INP", 13: "SGND", 14: "GND", 15: "XA", 16: "XB", 17: "VDRV", 18: "FLT", 19: "OUT4", 20: "VPWR", 21: "GND"},
     (31.5, 14.5), rot=0, lcsc="C1855776", desc="ultrasonic driver + log-amp receiver")
part("R7", "10R", "Resistor_SMD:R_0805_2012Metric", {1: "VBOOST", 2: "VPWR"}, (25.0, 7.5), rot=0, lcsc="verify", desc="RPWR (datasheet 8-1), 0805")
part("C11", "100nF 50V", "Capacitor_SMD:C_0603_1608Metric", {1: "VPWR", 2: "GND"}, (28.5, 9.5), rot=0, lcsc="C14663", desc="CPWR1 at pin 20")
part("C12", "2.2uF 50V", C0805, {1: "VDRV", 2: "GND"}, (37.0, 11.0), rot=0, lcsc="verify", desc="CPWR2 VDRV storage 0805 X7R (shield: 2 uF 40 V 1206)")
part("C13", "10nF", C0603, {1: "3V3", 2: "GND"}, (29.0, 19.5), rot=0, lcsc="verify-0402", desc="CVDD at pin 10")
part("C14", "1uF", C0603, {1: "3V3", 2: "GND"}, (32.0, 19.5), rot=0, lcsc="verify-0402", desc="VDD bulk")
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# =====================================================================================================================
# v0.3: ESP32 integrated (ESP32-WROOM-32UE, U.FL -> coax to the head SMA), USB-C + CH340C with auto-reset,
#       optional LoRa (Ai-Thinker Ra-01SH, SX1262) + U.FL. One PCB, two BOMs: "tipup" (no LoRa) and "lora" (all).
#       Pin map keeps the existing sensor_wroom firmware: SPI 18/19/23, TUSS CS 5, IO1 26, IO2 25, VOUT 36,
#       HALL 27, LED 2, VBAT 34.  New: OUT4 32, BOOST_EN 33, VPWR_ADC 35, NTC 39, BTN 15,
#       LoRa NSS 4, DIO1 16, RXEN 17, RST 21, BUSY 22, TXEN 13 (SPI shared with the TUSS4470).
# =====================================================================================================================
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part("C32", "1uF", C06, {1: "EN", 2: "GND"}, (22.0, 10.0), lcsc="C15849", desc="EN delay")
part("R21", "10k", R06, {1: "3V3", 2: "IO0"}, (22.0, 12.0), lcsc="C25804", desc="IO0 pull-up")
part("R22", "2.2k", R06, {1: "LED", 2: "LED_A"}, (22.0, 14.0), lcsc="C4190")
part("D6", "red", "LED_SMD:LED_0603_1608Metric", {1: "GND", 2: "LED_A"}, (22.0, 16.0), lcsc="C2286", desc="status LED (GPIO2, low at boot)")
# --- USB-C + CH340C + auto-reset (CH340 powered from VBUS through its own 3.3 V LDO: zero drain on the battery)
part("J5", "USB-C", "Connector_USB:USB_C_Receptacle_HRO_TYPE-C-31-M-12",
     {"A1": "GND", "B12": "GND", "A12": "GND", "B1": "GND", "S1": "GND", "A4": "VBUS", "B9": "VBUS", "A9": "VBUS", "B4": "VBUS",
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
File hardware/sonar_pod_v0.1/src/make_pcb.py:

"""Build sonar_pod.kicad_pcb (KiCad 7 format) from design.py with the pcbnew API: footprints from the
KiCad 7 library (+ a generated DSJ0014A), nets, placement, board outline, GND/SGND zones."""
import pcbnew, os, sys
from pcbnew import FromMM as mm, VECTOR2I, wxPoint
sys.path.insert(0, os.path.dirname(__file__))
import design as D

LIB = "/usr/share/kicad/footprints"
OUT = os.path.join(os.path.dirname(__file__), "out")
os.makedirs(OUT, exist_ok=True)

board = pcbnew.BOARD()
ds = board.GetDesignSettings()
ds.m_TrackMinWidth = mm(0.2); ds.m_ViasMinSize = mm(0.6); ds.m_MinThroughDrill = mm(0.2)
ds.m_MinClearance = mm(0.2)
# net classes: default 0.25 track / 0.2 clearance; power wider (set later by freerouting rules)
try:
    nc = ds.m_NetSettings.m_DefaultNetClass
    nc.SetTrackWidth(mm(0.25)); nc.SetClearance(mm(0.2)); nc.SetViaDiameter(mm(0.7)); nc.SetViaDrill(mm(0.35))
except Exception as e: print("netclass:", e)

# ---- nets
netinfo = {}
def net(name):
    if name not in netinfo:
        ni = pcbnew.NETINFO_ITEM(board, name)
        board.Add(ni); ni.thisown = 0
        netinfo[name] = board.GetNetInfo().GetNetItem(name)
    return netinfo[name]
for name in D.nets(): net(name)

# ---- custom footprint: TI DSJ0014A (VSON-14, 3.0 x 4.0 mm, 0.5 pitch, 7 pins per long side)
# ASSUMPTIONS TO VERIFY against TI drawing DSJ0014A: pad centres +-1.45 mm (x), pads 0.85 x 0.28, EP 1.6 x 2.6
def make_dsj0014a():
    fp = pcbnew.FOOTPRINT(board)
    fp.SetFPID(pcbnew.LIB_ID("SonarPod", "Texas_DSJ0014A"))
    fp.SetAttributes(pcbnew.FP_SMD)
    def pad(num, x, y, w, h):
        p = pcbnew.PAD(fp); p.SetNumber(str(num)); p.SetShape(pcbnew.PAD_SHAPE_ROUNDRECT); p.SetRoundRectRadiusRatio(0.2)
        p.SetAttribute(pcbnew.PAD_ATTRIB_SMD); p.SetSize(VECTOR2I(mm(w), mm(h))); p.SetPos0(VECTOR2I(mm(x), mm(y))); p.SetPosition(VECTOR2I(mm(x), mm(y)))
        p.SetLayerSet(pcbnew.PAD.SMDMask()); fp.Add(p); return p
    for i in range(7):
        y = (i - 3) * 0.5
        pad(1 + i, -1.45, y, 0.85, 0.28)        # pins 1-7 left side, top to bottom
        pad(14 - i, 1.45, y, 0.85, 0.28)        # pins 8-14 right side, bottom to top
    pad(15, 0, 0, 1.6, 2.6)                     # exposed pad = PGND
    for (x0, y0, x1, y1) in [(-1.5, -2.0, 1.5, -2.0), (-1.5, 2.0, 1.5, 2.0)]:
        s = pcbnew.FP_SHAPE(fp); s.SetShape(pcbnew.SHAPE_T_SEGMENT); s.SetStart0(VECTOR2I(mm(x0), mm(y0))); s.SetEnd0(VECTOR2I(mm(x1), mm(y1))); s.SetStart(VECTOR2I(mm(x0), mm(y0))); s.SetEnd(VECTOR2I(mm(x1), mm(y1)))
        s.SetLayer(pcbnew.F_SilkS); s.SetWidth(mm(0.12)); fp.Add(s)
    c = pcbnew.FP_SHAPE(fp); c.SetShape(pcbnew.SHAPE_T_CIRCLE); c.SetStart0(VECTOR2I(mm(-2.3), mm(-1.5))); c.SetEnd0(VECTOR2I(mm(-2.1), mm(-1.5))); c.SetStart(VECTOR2I(mm(-2.3), mm(-1.5))); c.SetEnd(VECTOR2I(mm(-2.1), mm(-1.5))); c.SetLayer(pcbnew.F_SilkS); c.SetWidth(mm(0.15)); fp.Add(c)
    for ly, (w, h) in ((pcbnew.F_CrtYd, (4.2, 5.2)),):
        r = pcbnew.FP_SHAPE(fp); r.SetShape(pcbnew.SHAPE_T_RECT); r.SetStart0(VECTOR2I(mm(-w / 2), mm(-h / 2))); r.SetEnd0(VECTOR2I(mm(w / 2), mm(h / 2))); r.SetStart(VECTOR2I(mm(-w / 2), mm(-h / 2))); r.SetEnd(VECTOR2I(mm(w / 2), mm(h / 2))); r.SetLayer(ly); r.SetWidth(mm(0.05)); fp.Add(r)
    return fp

# ---- place parts
for ref, p in D.P.items():
    lib, name = p["fp"].split(":")
    if lib == "SonarPod" and name == "Texas_DSJ0014A":
        fp = make_dsj0014a()
    else:
        fp = pcbnew.FootprintLoad(os.path.join(LIB, lib + ".pretty"), name)
        if fp is None: raise SystemExit(f"footprint not found {p['fp']}")
    fp.SetReference(ref); fp.SetValue(p["value"])
    x, y = p["pos"]
    fp.SetPosition(VECTOR2I(mm(x), mm(y)))
    if p["side"] == "B": fp.Flip(fp.GetPosition(), False)
    fp.SetOrientationDegrees(p["rot"])
    if p.get("dnp"): fp.SetAttributes(fp.GetAttributes() | pcbnew.FP_EXCLUDE_FROM_BOM | pcbnew.FP_EXCLUDE_FROM_POS_FILES)
    fp.SetProperty("LCSC", p.get("lcsc", ""))
    for pad in fp.Pads():
        num = pad.GetNumber()
        try: n = p["pins"].get(int(num), "")
        except ValueError: n = ""
        if n: pad.SetNet(net(n))
    fp.Reference().SetTextSize(VECTOR2I(mm(0.8), mm(0.8))); fp.Reference().SetTextThickness(mm(0.12))
    fp.Value().SetVisible(False)
    board.Add(fp)

# ---- outline (rounded rect)
W, H = D.BOARD_W, D.BOARD_H
def seg(x0, y0, x1, y1, layer=pcbnew.Edge_Cuts, w=0.1):
    s = pcbnew.PCB_SHAPE(board); s.SetShape(pcbnew.SHAPE_T_SEGMENT); s.SetStart(VECTOR2I(mm(x0), mm(y0))); s.SetEnd(VECTOR2I(mm(x1), mm(y1))); s.SetLayer(layer); s.SetWidth(mm(w)); board.Add(s)
r = 2.0
seg(r, 0, W - r, 0); seg(W, r, W, H - r); seg(W - r, H, r, H); seg(0, H - r, 0, r)
for (cx, cy, sx, sy) in [(r, r, -1, -1), (W - r, r, 1, -1), (W - r, H - r, 1, 1), (r, H - r, -1, 1)]:
    a = pcbnew.PCB_SHAPE(board); a.SetShape(pcbnew.SHAPE_T_ARC)
    a.SetCenter(VECTOR2I(mm(cx), mm(cy)))
    # arc from the horizontal tangent point to the vertical one, 90 deg
    if (sx, sy) == (-1, -1): a.SetStart(VECTOR2I(mm(cx), mm(cy - r))); a.SetArcAngleAndEnd(pcbnew.EDA_ANGLE(-90, pcbnew.DEGREES_T), False)
    elif (sx, sy) == (1, -1): a.SetStart(VECTOR2I(mm(cx + r), mm(cy))); a.SetArcAngleAndEnd(pcbnew.EDA_ANGLE(-90, pcbnew.DEGREES_T), False)
    elif (sx, sy) == (1, 1): a.SetStart(VECTOR2I(mm(cx), mm(cy + r))); a.SetArcAngleAndEnd(pcbnew.EDA_ANGLE(-90, pcbnew.DEGREES_T), False)
    else: a.SetStart(VECTOR2I(mm(cx - r), mm(cy))); a.SetArcAngleAndEnd(pcbnew.EDA_ANGLE(-90, pcbnew.DEGREES_T), False)
    a.SetLayer(pcbnew.Edge_Cuts); a.SetWidth(mm(0.1)); board.Add(a)

# ---- silkscreen title
t = pcbnew.PCB_TEXT(board); t.SetText("SONAR POD v0.1"); t.SetPosition(VECTOR2I(mm(W / 2), mm(H - 1.6))); t.SetLayer(pcbnew.F_SilkS); t.SetTextSize(VECTOR2I(mm(1.0), mm(1.0))); t.SetTextThickness(mm(0.15)); board.Add(t)

# ---- zones: GND both layers (whole board), SGND island on F.Cu around the receive pins / J2
def zone(netname, layer, pts, prio=0, clearance=0.25):
    z = pcbnew.ZONE(board); z.SetNet(net(netname)); z.SetLayer(layer)
    z.Outline().NewOutline()
    for (x, y) in pts: z.Outline().Append(mm(x), mm(y))
    z.SetAssignedPriority(prio); z.SetLocalClearance(mm(clearance)); z.SetMinThickness(mm(0.25))
    z.SetPadConnection(pcbnew.ZONE_CONNECTION_THERMAL); z.SetThermalReliefGap(mm(0.3)); z.SetThermalReliefSpokeWidth(mm(0.4))
    board.Add(z); return z
margin = 0.5
full = [(margin, margin), (W - margin, margin), (W - margin, H - margin), (margin, H - margin)]
if "--nozones" not in sys.argv:
    zone("GND", pcbnew.B_Cu, full, 0)
    zone("GND", pcbnew.F_Cu, full, 0)
# SGND island (F.Cu): INN cap, FLT cap, J2 shield pin, U1 pin 13; higher priority than GND
if "--nozones" not in sys.argv:
    zone("SGND", pcbnew.F_Cu, [(35.0, 14.0), (49.5, 14.0), (49.5, 21.0), (35.0, 21.0)], 1)

out = os.path.join(OUT, D.BOARD_NAME + ("_nozones" if "--nozones" in sys.argv else "") + ".kicad_pcb")
board.SetFileName(out)
pcbnew.SaveBoard(out, board)
print("saved", out, "footprints", len(board.GetFootprints()), "nets", board.GetNetCount())
